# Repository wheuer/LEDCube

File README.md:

# LED Cube

This repository tracks the most recent state of my LED cube project.

It's a mess and unpolished. For a more in depth look at the project and it's history see [my website](https://www.williamfheuer.com/project-portfolio).

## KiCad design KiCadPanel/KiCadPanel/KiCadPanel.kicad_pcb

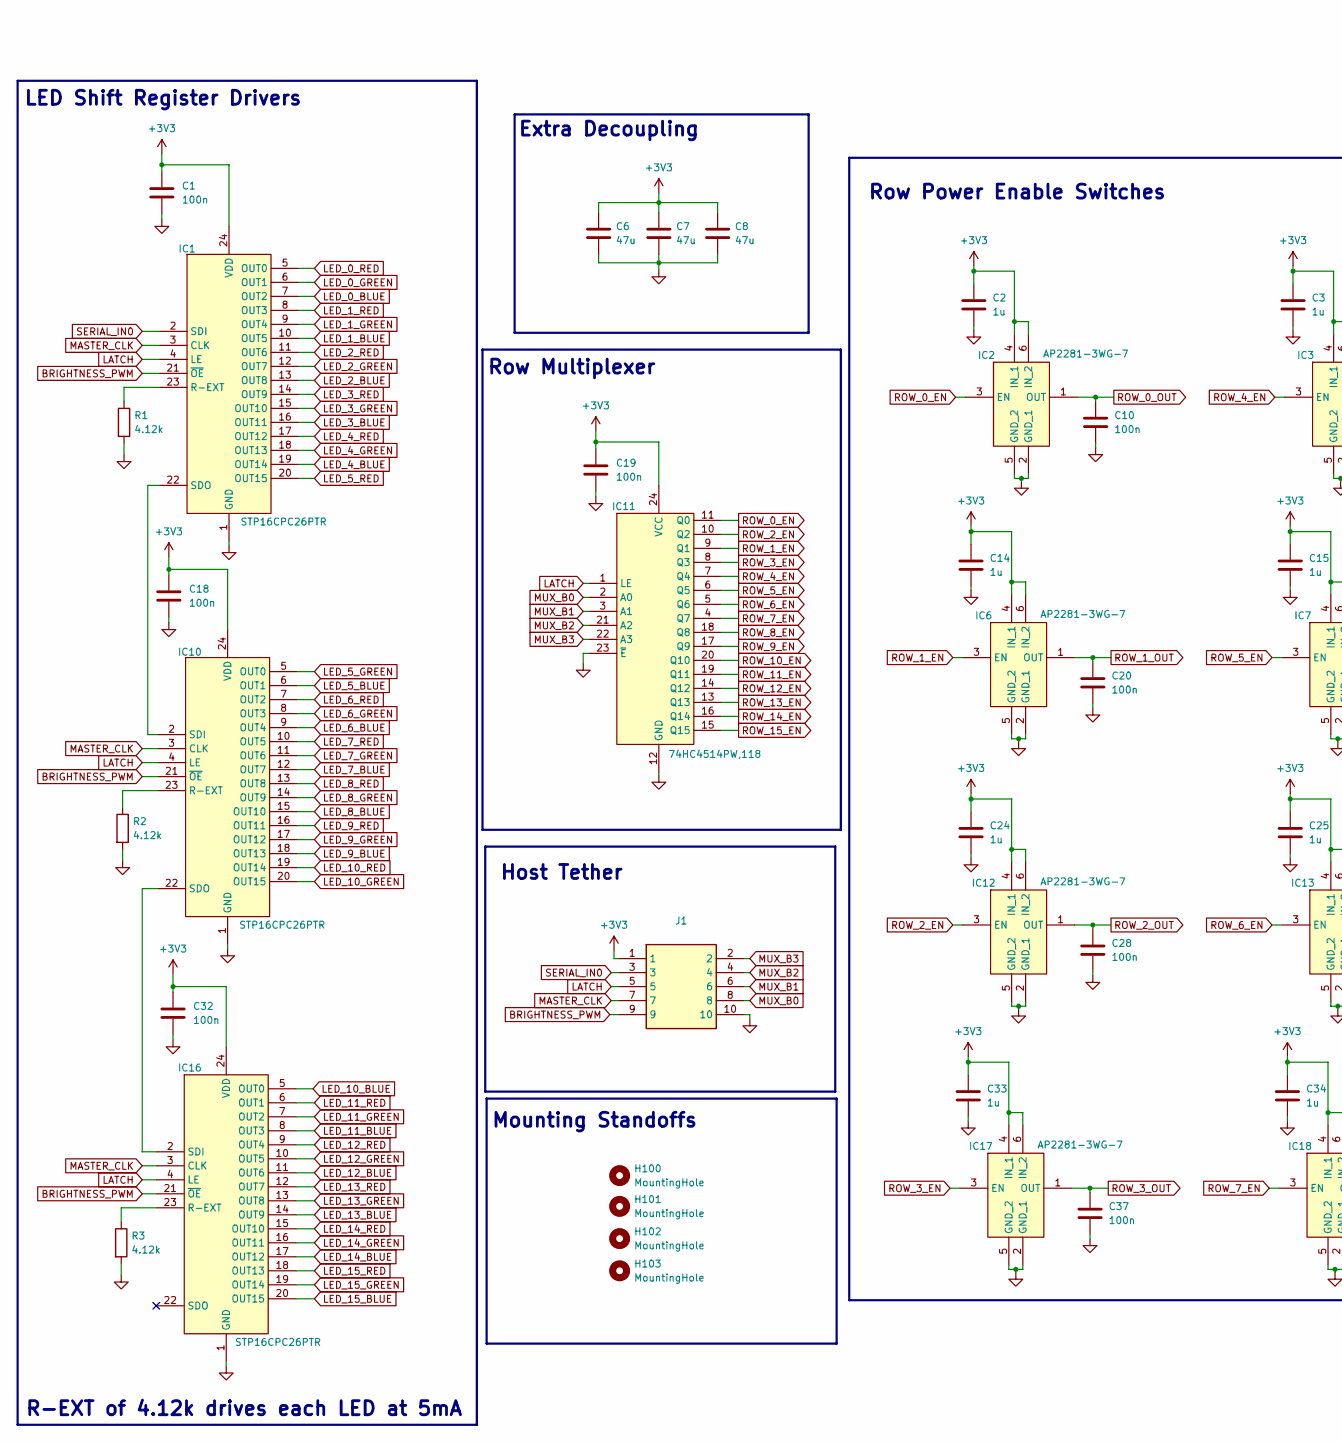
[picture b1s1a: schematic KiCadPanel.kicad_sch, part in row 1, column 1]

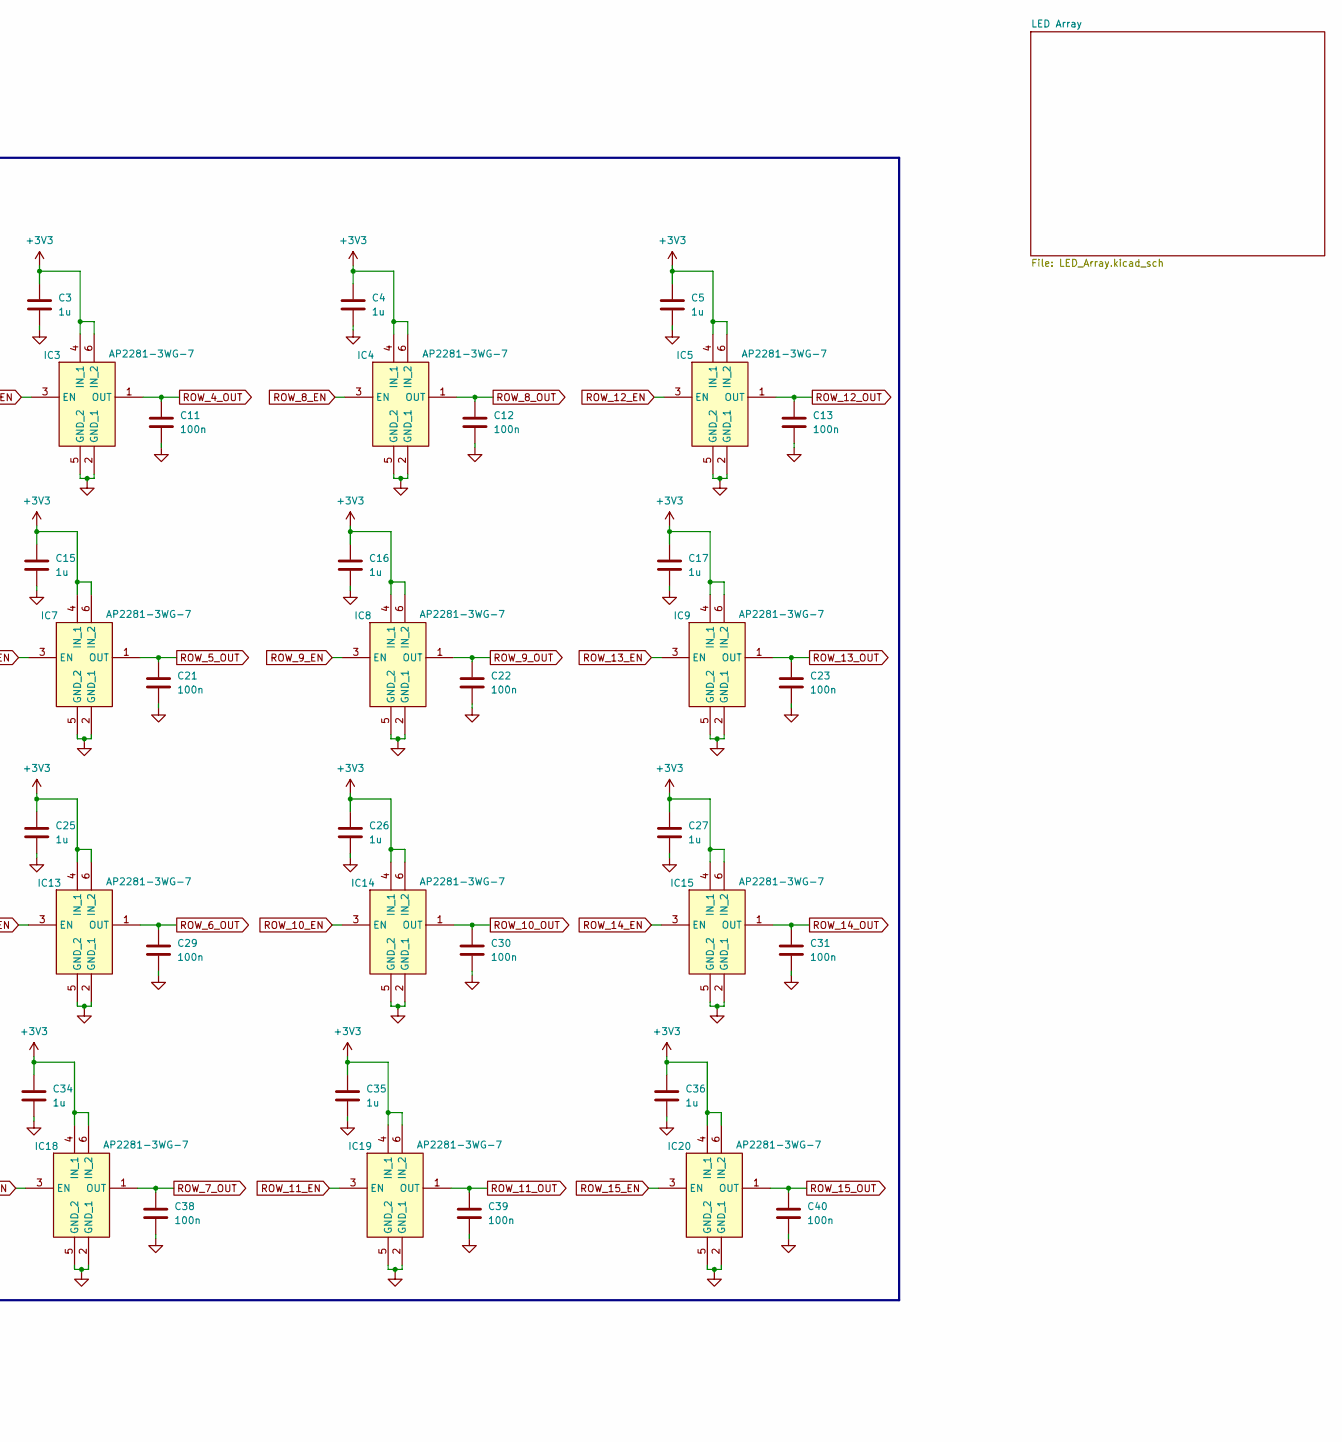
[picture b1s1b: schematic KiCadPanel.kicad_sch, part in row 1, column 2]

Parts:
C1, C10, C11, C12, C13, C18, C19, C20, C21, C22, C23, C28, C29, C30, C31, C32, C37, C38, C39, C40: 100n; C_0603_1608Metric
C2, C3, C4, C5, C14, C15, C16, C17, C24, C25, C26, C27, C33, C34, C35, C36: 1u; C_0603_1608Metric
C6, C7, C8: 47u; C_1206_3216Metric
H100, H101, H102, H103: MountingHole; Mounting_Wuerth_WA-SMSE-ExternalM3_H5mm_9771050360
IC1, IC10, IC16: STP16CPC26PTR; SOP64P600X173-24N; Mouser Part Number 511-STP16CPC26PTR
IC2, IC3, IC4, IC5, IC6, IC7, IC8, IC9, IC12, IC13, IC14, IC15, IC17, IC18, IC19, IC20: AP2281-3WG-7; SOT95P285X140-6N; Mouser Part Number 621-AP2281-3WG-7
IC11: 74HC4514PW,118; SOP65P640X110-24N; Mouser Part Number 771-HC4514PW118
J1: CNC_TECH_SMD_10POS; Manufacturer_Part_Number 15-91-0100
R1, R2, R3: 4.12k; R_0603_1608Metric

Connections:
+3V3: C1.1, C2.1, C3.1, C4.1, C5.1, C6.1, C7.1, C8.1, C14.1, C15.1, C16.1, C17.1, C18.1, C19.1, C24.1, C25.1, C26.1, C27.1, C32.1, C33.1, C34.1, C35.1, C36.1, IC1.24 (VDD), IC2.4 (IN_1), IC2.6 (IN_2), IC3.4 (IN_1), IC3.6 (IN_2), IC4.4 (IN_1), IC4.6 (IN_2), IC5.4 (IN_1), IC5.6 (IN_2), IC6.4 (IN_1), IC6.6 (IN_2), IC7.4 (IN_1), IC7.6 (IN_2), IC8.4 (IN_1), IC8.6 (IN_2), IC9.4 (IN_1), IC9.6 (IN_2), IC10.24 (VDD), IC11.24 (VCC), IC12.4 (IN_1), IC12.6 (IN_2), IC13.4 (IN_1), IC13.6 (IN_2), IC14.4 (IN_1), IC14.6 (IN_2), IC15.4 (IN_1), IC15.6 (IN_2), IC16.24 (VDD), IC17.4 (IN_1), IC17.6 (IN_2), IC18.4 (IN_1), IC18.6 (IN_2), IC19.4 (IN_1), IC19.6 (IN_2), IC20.4 (IN_1), IC20.6 (IN_2), J1.1
BRIGHTNESS_PWM: IC1.21 (~OE), IC10.21 (~OE), IC16.21 (~OE), J1.9
GND: C1.2, C2.2, C3.2, C4.2, C5.2, C6.2, C7.2, C8.2, C10.2, C11.2, C12.2, C13.2, C14.2, C15.2, C16.2, C17.2, C18.2, C19.2, C20.2, C21.2, C22.2, C23.2, C24.2, C25.2, C26.2, C27.2, C28.2, C29.2, C30.2, C31.2, C32.2, C33.2, C34.2, C35.2, C36.2, C37.2, C38.2, C39.2, C40.2, IC1.1 (GND), IC2.2 (GND_1), IC2.5 (GND_2), IC3.2 (GND_1), IC3.5 (GND_2), IC4.2 (GND_1), IC4.5 (GND_2), IC5.2 (GND_1), IC5.5 (GND_2), IC6.2 (GND_1), IC6.5 (GND_2), IC7.2 (GND_1), IC7.5 (GND_2), IC8.2 (GND_1), IC8.5 (GND_2), IC9.2 (GND_1), IC9.5 (GND_2), IC10.1 (GND), IC11.12 (GND), IC11.23 (~E), IC12.2 (GND_1), IC12.5 (GND_2), IC13.2 (GND_1), IC13.5 (GND_2), IC14.2 (GND_1), IC14.5 (GND_2), IC15.2 (GND_1), IC15.5 (GND_2), IC16.1 (GND), IC17.2 (GND_1), IC17.5 (GND_2), IC18.2 (GND_1), IC18.5 (GND_2), IC19.2 (GND_1), IC19.5 (GND_2), IC20.2 (GND_1), IC20.5 (GND_2), J1.10, R1.2, R2.2, R3.2
LATCH: IC1.4 (LE), IC10.4 (LE), IC11.1 (LE), IC16.4 (LE), J1.5
LED_0_BLUE: IC1.7 (OUT2); also elsewhere on the board
LED_0_GREEN: IC1.6 (OUT1); also elsewhere on the board
LED_0_RED: IC1.5 (OUT0); also elsewhere on the board
LED_1_BLUE: IC1.10 (OUT5); also elsewhere on the board
LED_1_GREEN: IC1.9 (OUT4); also elsewhere on the board
LED_1_RED: IC1.8 (OUT3); also elsewhere on the board
LED_2_BLUE: IC1.13 (OUT8); also elsewhere on the board
LED_2_GREEN: IC1.12 (OUT7); also elsewhere on the board
LED_2_RED: IC1.11 (OUT6); also elsewhere on the board
LED_3_BLUE: IC1.16 (OUT11); also elsewhere on the board
LED_3_GREEN: IC1.15 (OUT10); also elsewhere on the board
LED_3_RED: IC1.14 (OUT9); also elsewhere on the board
LED_4_BLUE: IC1.19 (OUT14); also elsewhere on the board
LED_4_GREEN: IC1.18 (OUT13); also elsewhere on the board
LED_4_RED: IC1.17 (OUT12); also elsewhere on the board
LED_5_BLUE: IC10.6 (OUT1); also elsewhere on the board
LED_5_GREEN: IC10.5 (OUT0); also elsewhere on the board
LED_5_RED: IC1.20 (OUT15); also elsewhere on the board
LED_6_BLUE: IC10.9 (OUT4); also elsewhere on the board
LED_6_GREEN: IC10.8 (OUT3); also elsewhere on the board
LED_6_RED: IC10.7 (OUT2); also elsewhere on the board
LED_7_BLUE: IC10.12 (OUT7); also elsewhere on the board
LED_7_GREEN: IC10.11 (OUT6); also elsewhere on the board
LED_7_RED: IC10.10 (OUT5); also elsewhere on the board
LED_8_BLUE: IC10.15 (OUT10); also elsewhere on the board
LED_8_GREEN: IC10.14 (OUT9); also elsewhere on the board
LED_8_RED: IC10.13 (OUT8); also elsewhere on the board
LED_9_BLUE: IC10.18 (OUT13); also elsewhere on the board
LED_9_GREEN: IC10.17 (OUT12); also elsewhere on the board
LED_9_RED: IC10.16 (OUT11); also elsewhere on the board
LED_10_BLUE: IC16.5 (OUT0); also elsewhere on the board
LED_10_GREEN: IC10.20 (OUT15); also elsewhere on the board
LED_10_RED: IC10.19 (OUT14); also elsewhere on the board
LED_11_BLUE: IC16.8 (OUT3); also elsewhere on the board
LED_11_GREEN: IC16.7 (OUT2); also elsewhere on the board
LED_11_RED: IC16.6 (OUT1); also elsewhere on the board
LED_12_BLUE: IC16.11 (OUT6); also elsewhere on the board
LED_12_GREEN: IC16.10 (OUT5); also elsewhere on the board
LED_12_RED: IC16.9 (OUT4); also elsewhere on the board
LED_13_BLUE: IC16.14 (OUT9); also elsewhere on the board
LED_13_GREEN: IC16.13 (OUT8); also elsewhere on the board
LED_13_RED: IC16.12 (OUT7); also elsewhere on the board
LED_14_BLUE: IC16.17 (OUT12); also elsewhere on the board
LED_14_GREEN: IC16.16 (OUT11); also elsewhere on the board
LED_14_RED: IC16.15 (OUT10); also elsewhere on the board
LED_15_BLUE: IC16.20 (OUT15); also elsewhere on the board
LED_15_GREEN: IC16.19 (OUT14); also elsewhere on the board
LED_15_RED: IC16.18 (OUT13); also elsewhere on the board
MASTER_CLK: IC1.3 (CLK), IC10.3 (CLK), IC16.3 (CLK), J1.7
MUX_B0: IC11.2 (A0), J1.8
MUX_B1: IC11.3 (A1), J1.6
MUX_B2: IC11.21 (A2), J1.4
MUX_B3: IC11.22 (A3), J1.2
unnamed: IC1.23 (R-EXT), R1.1
unnamed: IC1.22 (SDO), IC10.2 (SDI)
unnamed: IC10.23 (R-EXT), R2.1
unnamed: IC10.22 (SDO), IC16.2 (SDI)
unnamed: IC16.23 (R-EXT), R3.1
ROW_0_EN: IC2.3 (EN), IC11.11 (Q0)
ROW_0_OUT: C10.1, IC2.1 (OUT); also elsewhere on the board
ROW_1_EN: IC6.3 (EN), IC11.9 (Q1)
ROW_1_OUT: C20.1, IC6.1 (OUT); also elsewhere on the board
ROW_2_EN: IC11.10 (Q2), IC12.3 (EN)
ROW_2_OUT: C28.1, IC12.1 (OUT); also elsewhere on the board
ROW_3_EN: IC11.8 (Q3), IC17.3 (EN)
ROW_3_OUT: C37.1, IC17.1 (OUT); also elsewhere on the board
ROW_4_EN: IC3.3 (EN), IC11.7 (Q4)
ROW_4_OUT: C11.1, IC3.1 (OUT); also elsewhere on the board
ROW_5_EN: IC7.3 (EN), IC11.6 (Q5)
ROW_5_OUT: C21.1, IC7.1 (OUT); also elsewhere on the board
ROW_6_EN: IC11.5 (Q6), IC13.3 (EN)
ROW_6_OUT: C29.1, IC13.1 (OUT); also elsewhere on the board
ROW_7_EN: IC11.4 (Q7), IC18.3 (EN)
ROW_7_OUT: C38.1, IC18.1 (OUT); also elsewhere on the board
ROW_8_EN: IC4.3 (EN), IC11.18 (Q8)
ROW_8_OUT: C12.1, IC4.1 (OUT); also elsewhere on the board
ROW_9_EN: IC8.3 (EN), IC11.17 (Q9)
ROW_9_OUT: C22.1, IC8.1 (OUT); also elsewhere on the board
ROW_10_EN: IC11.20 (Q10), IC14.3 (EN)
ROW_10_OUT: C30.1, IC14.1 (OUT); also elsewhere on the board
ROW_11_EN: IC11.19 (Q11), IC19.3 (EN)
ROW_11_OUT: C39.1, IC19.1 (OUT); also elsewhere on the board
ROW_12_EN: IC5.3 (EN), IC11.14 (Q12)
ROW_12_OUT: C13.1, IC5.1 (OUT); also elsewhere on the board
ROW_13_EN: IC9.3 (EN), IC11.13 (Q13)
ROW_13_OUT: C23.1, IC9.1 (OUT); also elsewhere on the board
ROW_14_EN: IC11.16 (Q14), IC15.3 (EN)
ROW_14_OUT: C31.1, IC15.1 (OUT); also elsewhere on the board
ROW_15_EN: IC11.15 (Q15), IC20.3 (EN)
ROW_15_OUT: C40.1, IC20.1 (OUT); also elsewhere on the board
SERIAL_IN0: IC1.2 (SDI), J1.3

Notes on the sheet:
LED Shift Register Drivers
Row Power Enable Switches
R-EXT of 4.12k drives each LED at 5mA
Host Tether
Row Multiplexer
Extra Decoupling
Mounting Standoffs
